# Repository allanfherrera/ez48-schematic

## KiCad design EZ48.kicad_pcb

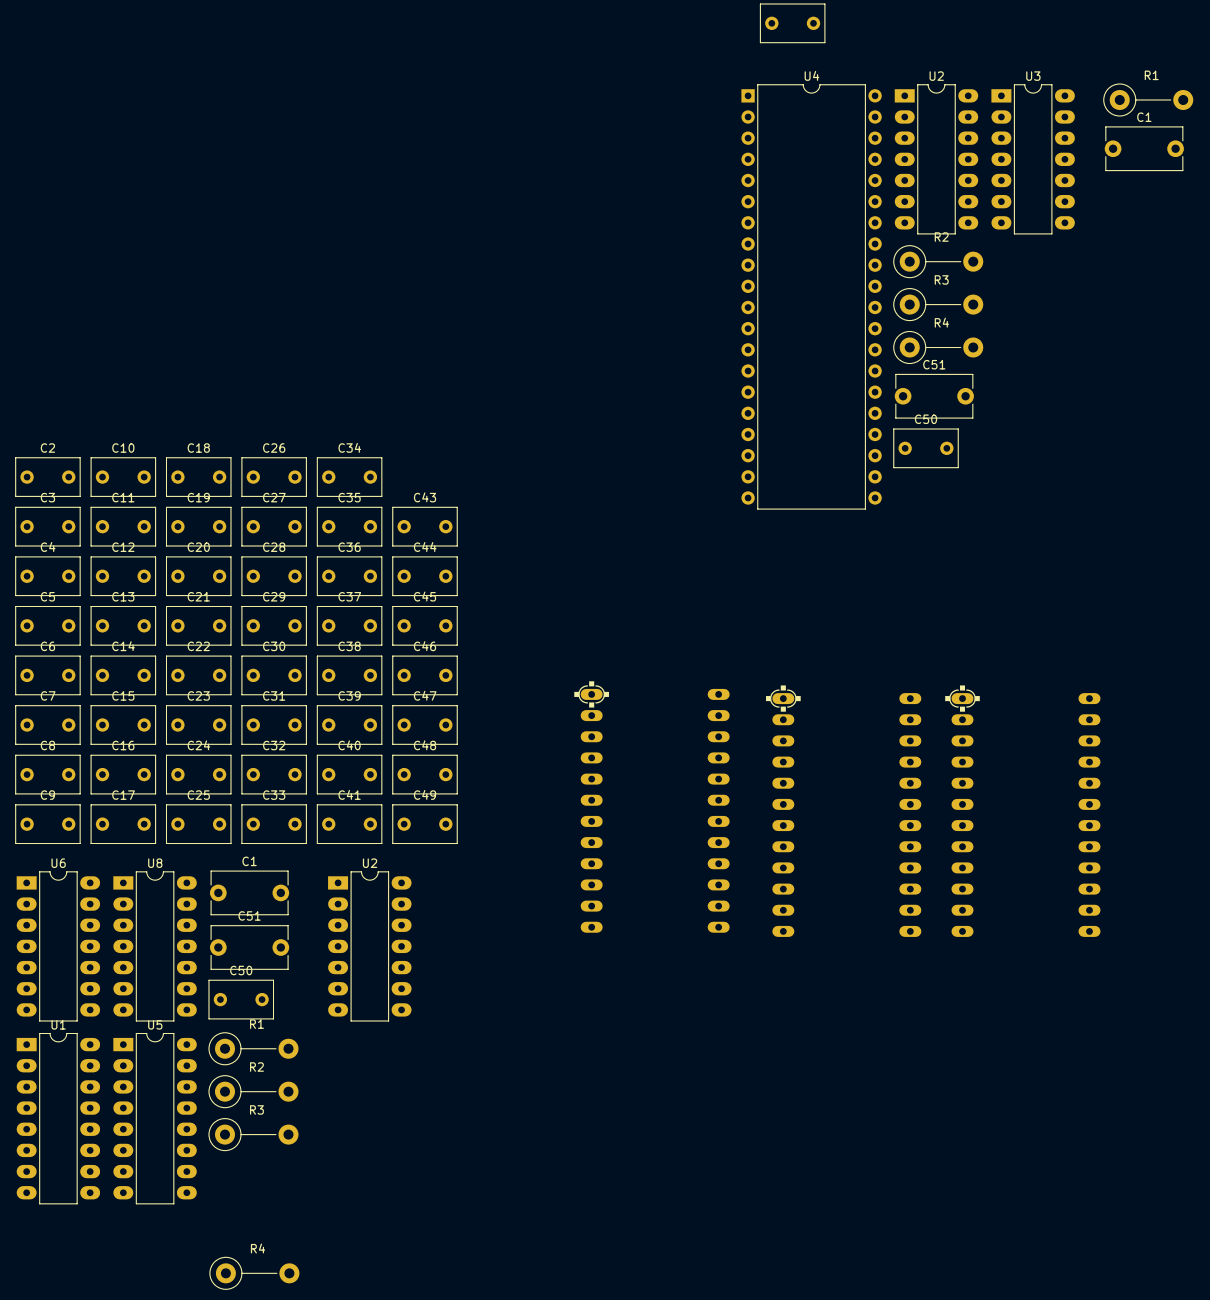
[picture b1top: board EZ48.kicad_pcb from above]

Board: 2 copper layers, 73 parts (0 on the bottom side), 21 nets, no tracks yet.

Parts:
C1, C1#2: 47uF; C_Disc_D9.0mm_W5.0mm_P7.50mm
C2, C3, C4, C5, C6, C7, C8, C9, C10, C11, C12, C13, C14, C15, C16, C17, C18, C19, C20, C21, C22, C23, C24, C25, C26, C27, C28, C29, C30, C31, C32, C33, C34, C35, C36, C37, C38, C39, C40, C41, C42, C43, C44, C45, C46, C47, C48, C49: 47uF; C_Disc_D7.5mm_W4.4mm_P5.00mm
C50, C50#2: 0.1uF; C_Disc_D7.5mm_W4.4mm_P5.00mm
C51, C51#2: 10 uF; C_Disc_D9.0mm_W5.0mm_P7.50mm
IC1, IC2, IC3: 2732; DIL24
R1, R1#2: 47Ohm; R_Axial_DIN0411_L9.9mm_D3.6mm_P7.62mm_Vertical
R2, R2#2: 1M Ohm; R_Axial_DIN0411_L9.9mm_D3.6mm_P7.62mm_Vertical
R3, R3#2: 47K Ohm; R_Axial_DIN0411_L9.9mm_D3.6mm_P7.62mm_Vertical
R4, R4#2: 1K Ohm; R_Axial_DIN0411_L9.9mm_D3.6mm_P7.62mm_Vertical
U1: 74LS139; DIP-16_W7.62mm_LongPads
U2, U2#2, U8: 74LS06; DIP-14_W7.62mm_LongPads
U3, U6: NE556; DIP-14_W7.62mm_LongPads
U4: 6502; DIP-40_W15.24mm
U5: 74LS138; DIP-16_W7.62mm_LongPads

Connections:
+5VDC: C2.1, C3.1, C4.1, C5.1, C6.1, C7.1, C8.1, C9.1, C10.1, C11.1, C12.1, C13.1, C14.1, C15.1, C16.1, C17.1, C18.1, C19.1, C20.1, C21.1, C22.1, C23.1, C24.1, C25.1, C26.1, C27.1, C28.1, C29.1, C30.1, C31.1, C32.1, C33.1, C34.1, C35.1, C36.1, C37.1, C38.1, C39.1, C40.1, C41.1, C42.1, C43.1, C44.1, C45.1, C46.1, C47.1, C48.1, C49.1, C50.2, C50#2.2, R2.1, R2#2.1, R3.2, R3#2.2, R4.1, R4#2.1, U1.16 (VCC), U2.14 (VCC), U3.4 (R), U3.14 (VCC), U4.8 (VCC), U5.16 (VCC), U6.10 (R), U6.14 (VCC), U8.14 (VCC)
A8: U4.17 (A8), U5.3 (A2)
A9: U4.18 (A9), U5.2 (A1)
A10: U4.19 (A10), U5.1 (A0)
A11: U4.20 (A11), U5.4 (E1)
A12: U1.2 (A0), U4.22 (A12)
A13: U1.3 (A1), U4.23 (A13)
A14: U1.14 (A0), U4.24 (A14)
A15: U1.13 (A1), U4.25 (A15)
GND: C1.1, C1#2.1, C2.2, C3.2, C4.2, C5.2, C6.2, C7.2, C8.2, C9.2, C10.2, C11.2, C12.2, C13.2, C14.2, C15.2, C16.2, C17.2, C18.2, C19.2, C20.2, C21.2, C22.2, C23.2, C24.2, C25.2, C26.2, C27.2, C28.2, C29.2, C30.2, C31.2, C32.2, C33.2, C34.2, C35.2, C36.2, C37.2, C38.2, C39.2, C40.2, C41.2, C42.2, C43.2, C44.2, C45.2, C46.2, C47.2, C48.2, C49.2, C50.1, C50#2.1, C51.2, C51#2.2, R1.2, R1#2.2, U1.8 (GND), U1.15 (E), U2.7 (GND), U3.7 (GND), U4.1 (VSS), U4.21 (VSS), U5.6 (E3), U5.8 (GND), U6.7 (GND), U8.7 (GND)
unnamed: C1.2, C1#2.2, R1.1, R1#2.1
unnamed: U1.1 (E), U1.9 (O3)
unnamed: U1.4 (O0), U5.5 (E2)
unnamed: C51.1, R3#2.1, U3.1 (DIS), U3.2 (THR)
unnamed: U2.1, U3.5 (Q)
unnamed: R2.2, U3.6 (TR)
unnamed: C51#2.1, R3.1, U6.12 (THR), U6.13 (DIS)
unnamed: U6.9 (Q), U8.1
unnamed: R2#2.2, U6.8 (TR)
RESET: R4.2, U8.2
~RESET: R4#2.2, U2.2, U4.40 (~RES)

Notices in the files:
parts and their libraries:
Copyright ©07 Jan 2013, by:
Robert \"The R.A.T.\" Allen Turner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
